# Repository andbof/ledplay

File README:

Ledplay is a small project aimed as a childrens toy. It uses a Cortex M0+
(Kinetis KE04, MKE04Z8VWJ4) to light button leds in binary order, waiting for
them to be pressed. When a complete number has been pressed, it progresses to
the next, until all have been exhausted. It then resets from one.

Copyright (C) 2016 Andreas Bofjäll <andreas@gazonk.org>, see LICENSE for
licensing details.

DESIGN RATIONALE

  Power efficiency was paramount, but I still wanted to retain programmability
  and flexibility for future use cases. The whole circuit is running at around
  130 uA when no leds are lit, giving it a runtime of about 1 to 1.5 years on
  two double AA batteries. There are no current limiting resistors for the leds
  and the led dc-dc drives them using constant voltage, but they won't be lit
  long enough for their resistance drop to become a problem.

  The led dc-dc is a SEPIC because originally, the leds would be driven with a
  lower voltage, but they turned out to be too dim.

SCHEMATICS AND PCB

  Schematic and PCB are made in Kicad. The PCB is a four layer board (mostly
  because I wanted to play with multilayer boards).

COMPILING

  Enter the src directory and run "make". You need a standard gcc arm toolchain
  (arm-none-eabi-*) installed, but nothing else. Ledplay does not use CMSIS.

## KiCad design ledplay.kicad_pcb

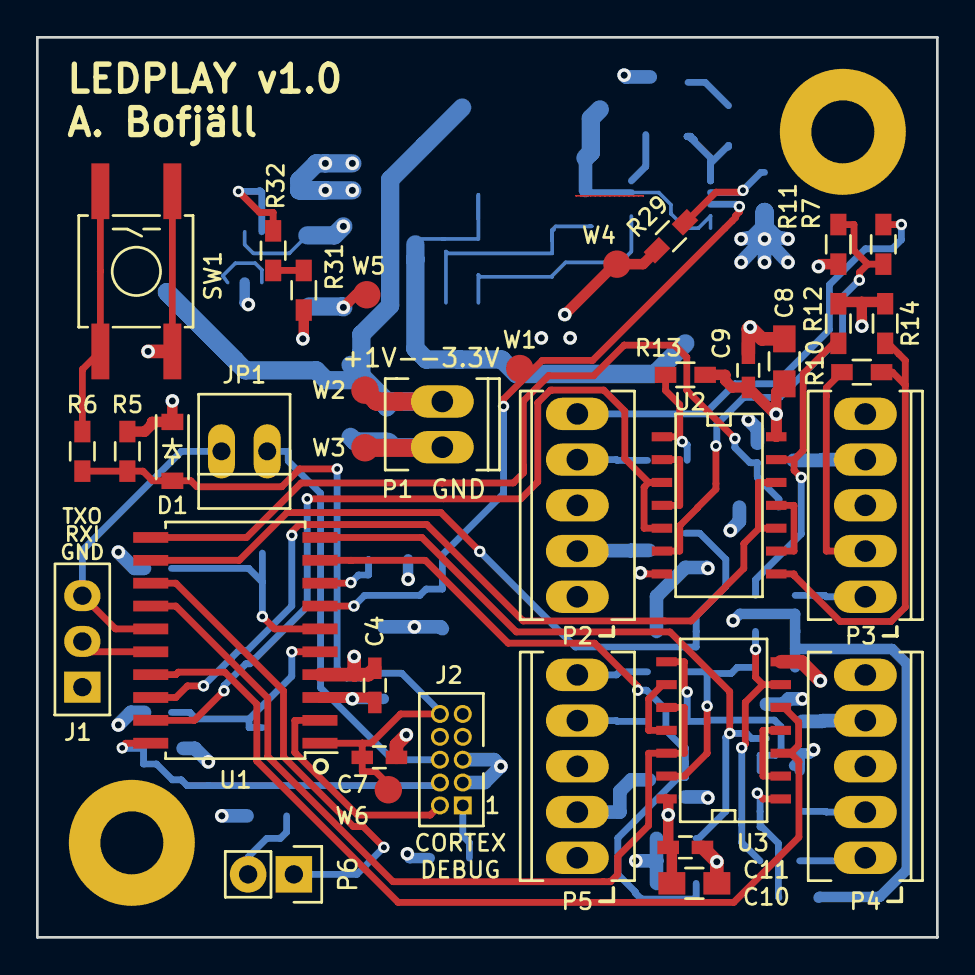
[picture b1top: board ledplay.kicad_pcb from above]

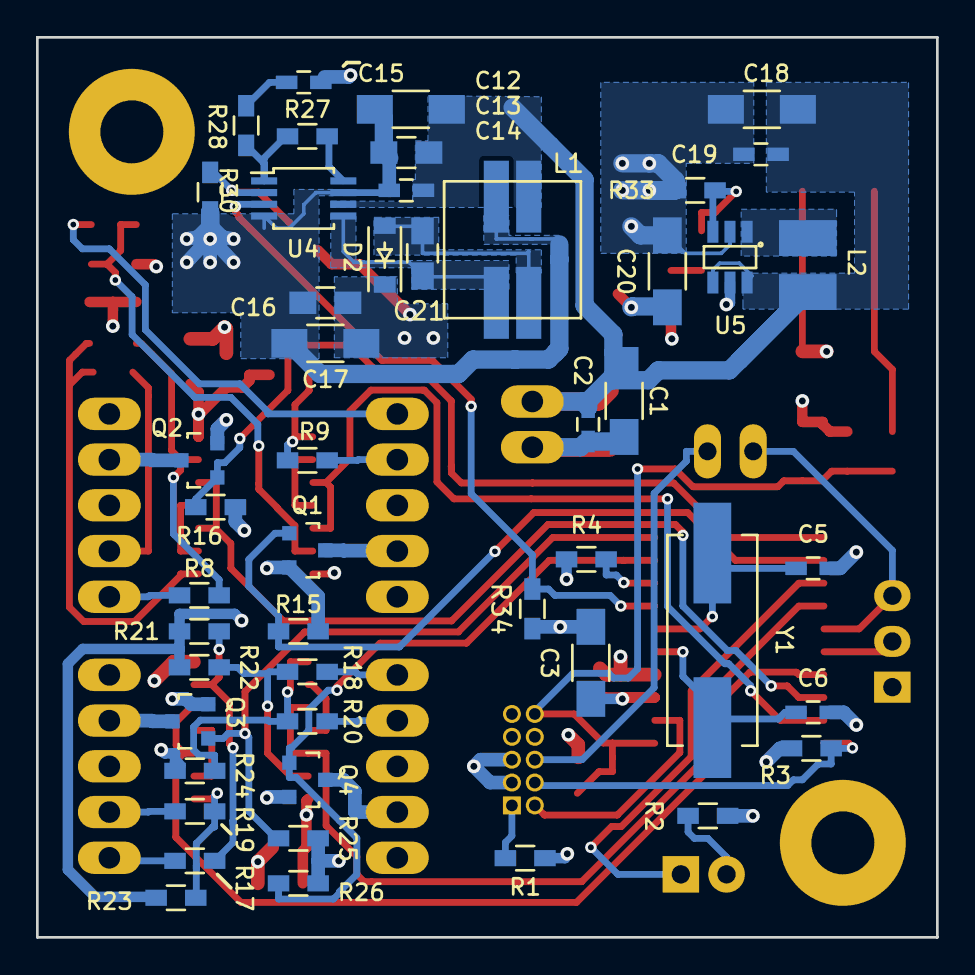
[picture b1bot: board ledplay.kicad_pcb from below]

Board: 4 copper layers, 50.0 x 50.0 mm, 87 parts (48 on the bottom side), 59 nets.

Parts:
C1, C12, C17: 22 uF; C_1206_HandSoldering
C2, C4, C7, C9, C11, C14, C19: 100 nF; C_0603_HandSoldering
C3, C18, C20: 10 uF; C_1206_HandSoldering
C5, C6: 18 pF; C_0603_HandSoldering
C8, C10, C13, C16, C21: 1 uF; C_0805_HandSoldering
C15: 220 pF; C_0603_HandSoldering
D1, D2: MBR0520LT3G; SOD-123
J1: UART_CONN
J2: CORTEX_DEBUG
JP1: JUMPER; PINHEAD1-2
L1: 22 uH; SRF0703
L2: 6.8 uH; INDUCTOR_1812
MP1, MP2: PLATED_HOLE
P1: PWRCON_01X02; Socket_MOLEX-KK-RM2-54mm_Lock_2pin_straight
P2, P3, P4, P5: CONN_01X05; Socket_MOLEX-KK-RM2-54mm_Lock_5pin_straight
P6: CONN_01X02; Pin_Header_Straight_1x02
Q1, Q2, Q3, Q4: BSS138; SOT-23
R1, R5, R27: NP; R_0603_HandSoldering
R2, R3, R4: 10k; R_0603_HandSoldering
R6: 330; R_0603_HandSoldering
R7, R8, R9, R10, R17, R18, R19, R20: 1k; R_0603_HandSoldering
R11, R12, R13, R14, R15, R16, R21, R22, R23, R24, R25, R26, R34: 100k; R_0603_HandSoldering
R28: 220k; R_0603_HandSoldering
R29: 560k; R_0603_HandSoldering
R30: 787k; R_0603_HandSoldering
R31: 1M; R_0603_HandSoldering
R32: 20k; R_0603_HandSoldering
R33: 604k; R_0603_HandSoldering
SW1: SW_PUSH; SW_KSEM31G
U1: MKE04Z8VWJ4; SOIC-20_7.5x12.8mm_Pitch1.27mm
U2, U3: 4093; SOIC-14_N
U4: LT1610; MSOP-8
U5: LTC3429; SOT-23
W1, W2, W3, W4, W5, W6: TEST_1P; Measurement_Point_Round-SMD-Pad_Small
Y1: 14.7456 MHz; Crystal_HC49-SD_SMD

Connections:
+3V3: C3.1, C4.1, C8.1, C9.1, C10.1, C11.1, C20.1, D1.1, R1.1, R4.1, R5.1, R11.1, R12.1, R13.1, R14.1, R21.1, R22.1, R23.1, R24.1, R31.1, U1.3, U2.14, U3.14, U5.5, W5.1
+BATT: C1.1, C2.1, C12.1, C13.1, C14.1, C18.1, C19.1, L1.3, L2.2, P1.1, U4.6, U5.4, U5.6, W2.1
+LED: C16.1, C17.1, D2.1, P2.1, P3.1, P4.1, P5.1, R29.1, W4.1
/AUX: P6.1, U1.13
/EXTAL: C6.1, U1.5, Y1.2
/LEDSWITCH_CTRL/GND_LED1: P2.2, Q1.3
/LEDSWITCH_CTRL/GND_LED2: P3.2, Q2.3
/LEDSWITCH_CTRL/GND_LED3: P4.2, Q3.3
/LEDSWITCH_CTRL/GND_LED4: P5.2, Q4.3
/LEDSWITCH_CTRL/LED1_CTRL: Q1.1, R15.1, U1.12
/LEDSWITCH_CTRL/LED2_CTRL: Q2.1, R16.1, U1.11
/LEDSWITCH_CTRL/LED3_CTRL: Q3.1, R25.1, U1.10
/LEDSWITCH_CTRL/LED4_CTRL: Q4.1, R26.1, U1.9
/LEDSWITCH_CTRL/SW1_STATE: U1.19, U2.3, U2.5
/LEDSWITCH_CTRL/SW2_STATE: U1.18, U2.10, U2.12
/LEDSWITCH_CTRL/SW3_STATE: U1.17, U3.3, U3.5
/LEDSWITCH_CTRL/SW4_STATE: U1.14, U3.10, U3.12
/LED_POWER/~LED_SHDN: R34.1, U1.7, U4.3, W1.1
/NMI: R4.2, U1.8
/SWCLK: J2.4, R3.1, U1.20
/SWDIO: J2.2, U1.2
/UART0_RX: J1.2, U1.16
/UART0_TX: J1.3, JP1.2, U1.15
/XTAL: C5.1, U1.6, Y1.1
/~MCU_RESET: C7.1, D1.2, J2.10, R5.2, R6.2, U1.1, W6.1
GND: C1.2, C2.2, C3.2, C4.2, C5.2, C6.2, C7.2, C8.2, C9.2, C10.2, C11.2, C12.2, C13.2, C14.2, C15.2, C16.2, C17.2, C18.2, C19.2, C20.2, J1.1, J2.3, J2.5, L1.4, MP1.1, MP2.1, P1.2, P2.3, P3.3, P4.3, P5.3, Q1.2, Q2.2, Q3.2, Q4.2, R2.2, R3.2, R15.2, R16.2, R25.2, R26.2, R30.2, R33.2, R34.2, SW1.2, U1.4, U2.7, U3.7, U4.4, U4.7, U5.2, W3.1
unnamed: C15.1, R28.2
unnamed: C21.1, L1.1, U4.5
unnamed: C21.2, D2.2, L1.2
unnamed: J2.1, R1.2
unnamed: J2.6, JP1.1
unnamed: L2.1, U5.1
unnamed: P2.4, R9.2
unnamed: P2.5, R7.2
unnamed: P3.4, R10.2
unnamed: P3.5, R8.2
unnamed: P4.4, R19.2
unnamed: P4.5, R17.2
unnamed: P5.4, R20.2
unnamed: P5.5, R18.2
unnamed: P6.2, R2.1
unnamed: R6.1, SW1.1
unnamed: R10.1, R14.2, U2.8
unnamed: R7.1, R11.2, U2.6
unnamed: R8.1, R12.2, U2.13
unnamed: R9.1, R13.2, U2.1
unnamed: R17.1, R21.2, U3.6
unnamed: R18.1, R22.2, U3.13
unnamed: R19.1, R23.2, U3.1
unnamed: R20.1, R24.2, U3.8
unnamed: R27.1, U4.8
unnamed: R27.2, R28.1, U4.1
unnamed: R29.2, R30.1, U4.2
unnamed: R31.2, R32.1
unnamed: R32.2, R33.1, U5.3
unnamed: U2.2, U2.4
unnamed: U2.9, U2.11
unnamed: U3.2, U3.4
unnamed: U3.9, U3.11

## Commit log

2017-09-10 Fix layout and schema (as sent for production)
    This matches hardware revision v1.0 sent for production.
2017-09-10 Add layout and schematic
2017-09-10 Fix power connector polarity
    The power connector had the wrong polarity in the schematic. Fix it to
    avoid confusion.
2017-09-10 gitignore: add
2017-09-10 Fix erratas in layout and schematic
    For v1.1, a fix a few erratas found in the layout and schematic:
    - The CPU actively pulls the reset pin low when it goes into
    reset. This does not work with the reset circuitry in v1.0.
    Add D3 to fix this.
    - Update DC-DC resistor values to match led drive voltage.
    - Fix footprints.
2017-09-10 Add source code
2017-11-07 README: update design rationale
2017-11-07 LICENSE: clarify
